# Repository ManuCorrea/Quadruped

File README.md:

# RL Quadruped
This project is a robotic platform to use for education, development and research. 
Objectives: **democratize robotics** and **sim-to-real research**.

## Installation

If using stable baselines:

```
sudo apt-get update && sudo apt-get install cmake libopenmpi-dev python3-dev zlib1g-dev
```

```
pip3 install -r requeriments.txt
```

## Bill of Materials
* Nvidia Jetson Nano
* Arduino Mega
* TinyFPGA BX
* 12 x micro gear dc motors with encoders
* 2 x servos
* ADNS 3080 optical flow sensor
* GY-521
* 7-12V LiPo battery
* 10 x 3D printer endstops
### Tools
* 3D printer
* Soledering iron and solder wire
* M3 screws, nuts and self-locking nuts

## Building

For details and images you can check my [hackster project](https://www.hackster.io/_ManuCorrea_/rl-quadruped-0afbc3)

## Contributing
Pull requests are welcome. For major changes, please open an issue first to discuss what you would like to change.

Feel free to [contact me](https://twitter.com/_ManuCorrea_) directly if you are interested in the project.

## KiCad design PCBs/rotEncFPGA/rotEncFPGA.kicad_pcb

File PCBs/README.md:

# Description
In this folder there will be the KiCad projects of the differents PCBs.

## TODO Upgrades
- [ ] Use a different motor controller IC with PWM to control them with speed variation and implement it in a PCB design.
- [ ] Create PCB for plugging all endstops instead of the protoboard.
- [ ] Create an unique PCB with all electronics.

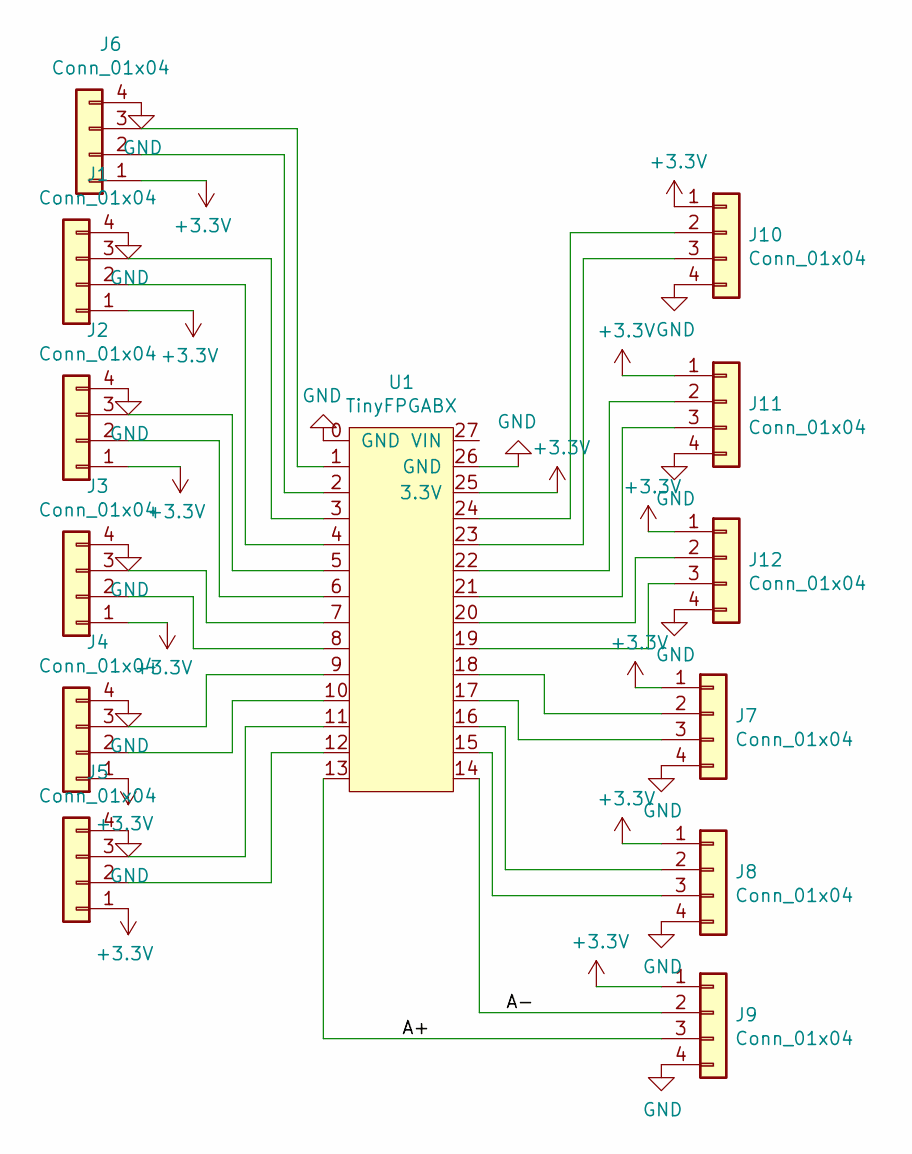
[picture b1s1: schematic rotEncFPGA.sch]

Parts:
J1, J2, J3, J4, J5, J6, J7, J8, J9, J10, J11, J12: Conn_01x04; PinSocket_1x04_P2.54mm_Vertical
U1: TinyFPGABX; tinyFPGABX

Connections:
+3V3: J1.1, J2.1, J3.1, J4.1, J5.1, J6.1, J7.1, J8.1, J9.1, J10.1, J11.1, J12.1, U1.25 (3.3V); also elsewhere on the board
/A+: J9.3, U1.13; also elsewhere on the board
/A-: J9.2, U1.14; also elsewhere on the board
GND: J1.4, J2.4, J3.4, J4.4, J5.4, J6.4, J7.4, J8.4, J9.4, J10.4, J11.4, J12.4, U1.0 (GND), U1.26 (GND); also elsewhere on the board
unnamed 4: J1.2, U1.4; also elsewhere on the board
unnamed 5: J1.3, U1.3; also elsewhere on the board
unnamed 6: J2.2, U1.6; also elsewhere on the board
unnamed 7: J2.3, U1.5; also elsewhere on the board
unnamed 8: J3.2, U1.8; also elsewhere on the board
unnamed 9: J3.3, U1.7; also elsewhere on the board
unnamed 10: J4.2, U1.10; also elsewhere on the board
unnamed 11: J4.3, U1.9; also elsewhere on the board
unnamed 12: J5.2, U1.12; also elsewhere on the board
unnamed 13: J5.3, U1.11; also elsewhere on the board
unnamed 14: J6.2, U1.2; also elsewhere on the board
unnamed 15: J6.3, U1.1; also elsewhere on the board
unnamed 16: J7.2, U1.18; also elsewhere on the board
unnamed 17: J7.3, U1.17; also elsewhere on the board
unnamed 18: J8.2, U1.16; also elsewhere on the board
unnamed 19: J8.3, U1.15; also elsewhere on the board
unnamed 20: J10.2, U1.24; also elsewhere on the board
unnamed 21: J10.3, U1.23; also elsewhere on the board
unnamed 22: J11.2, U1.22; also elsewhere on the board
unnamed 23: J11.3, U1.21; also elsewhere on the board
unnamed 24: J12.2, U1.20; also elsewhere on the board
unnamed 25: J12.3, U1.19; also elsewhere on the board

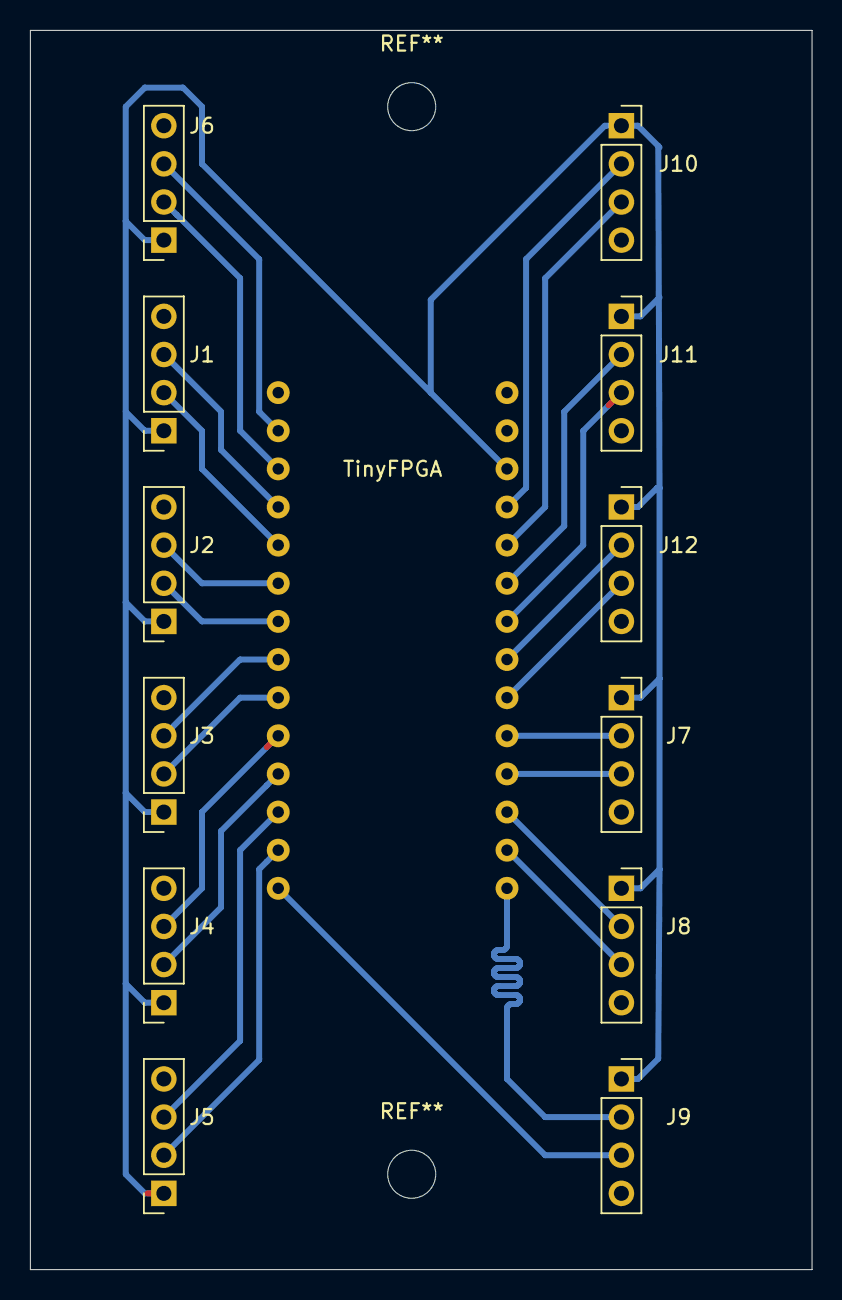
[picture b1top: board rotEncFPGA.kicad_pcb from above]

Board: 2 copper layers, 52.1 x 82.5 mm, 13 parts (0 on the bottom side), 26 nets.

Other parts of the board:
TinyFPGA: TinyFPGABX; tinyFPGABX

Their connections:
+3V3: TinyFPGA.25; also elsewhere on the board
/A+: TinyFPGA.13; also elsewhere on the board
/A-: TinyFPGA.14; also elsewhere on the board
GND: TinyFPGA.0, TinyFPGA.26; also elsewhere on the board
unnamed 4: TinyFPGA.4; also elsewhere on the board
unnamed 5: TinyFPGA.3; also elsewhere on the board
unnamed 6: TinyFPGA.6; also elsewhere on the board
unnamed 7: TinyFPGA.5; also elsewhere on the board
unnamed 8: TinyFPGA.8; also elsewhere on the board
unnamed 9: TinyFPGA.7; also elsewhere on the board
unnamed 10: TinyFPGA.10; also elsewhere on the board
unnamed 11: TinyFPGA.9; also elsewhere on the board
unnamed 12: TinyFPGA.12; also elsewhere on the board
unnamed 13: TinyFPGA.11; also elsewhere on the board
unnamed 14: TinyFPGA.2; also elsewhere on the board
unnamed 15: TinyFPGA.1; also elsewhere on the board
unnamed 16: TinyFPGA.18; also elsewhere on the board
unnamed 17: TinyFPGA.17; also elsewhere on the board
unnamed 18: TinyFPGA.16; also elsewhere on the board
unnamed 19: TinyFPGA.15; also elsewhere on the board
unnamed 20: TinyFPGA.24; also elsewhere on the board
unnamed 21: TinyFPGA.23; also elsewhere on the board
unnamed 22: TinyFPGA.22; also elsewhere on the board
unnamed 23: TinyFPGA.21; also elsewhere on the board
unnamed 24: TinyFPGA.20; also elsewhere on the board
unnamed 25: TinyFPGA.19; also elsewhere on the board

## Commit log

2020-01-24 Gimbal's code for ADNS 3080 added
2020-01-24 Added motorController but not tested, need to finish PCB.
2020-01-24 Added counter module and instantiation.
    Reg size needed for counter unknown so set as 4.
2020-02-07 Created gym env Need to add body orientation for rewards.
2020-02-17 Added model deploy to enviroment
2020-02-17 Script for behavior cloning dataset creation added.
2020-02-17 Updated rewards and added functionalities.
2020-02-17 Added behaviorCloningPretrain.py used for training an agent with the expert dataset.
2020-02-17 Added ROS package with URDF file and simplified STLs of Quadruped.
2020-02-17 Added args, comments and TODOs.
2020-02-17 Added quadruped STLs files.
2020-02-18 Added main README, STLs README and requeriments.txt
2020-02-18 TinyFPGA PCB added.
2020-02-18 Added Serial Tx.
2020-02-18 Added main jetson script for taking data and give orders.
2020-02-18 Added READMEs and Arduino program with functions to communicate with Jetson by Serial.
2020-08-08 Added new TODO comments.
2020-08-09 Improved simulation's time management.
